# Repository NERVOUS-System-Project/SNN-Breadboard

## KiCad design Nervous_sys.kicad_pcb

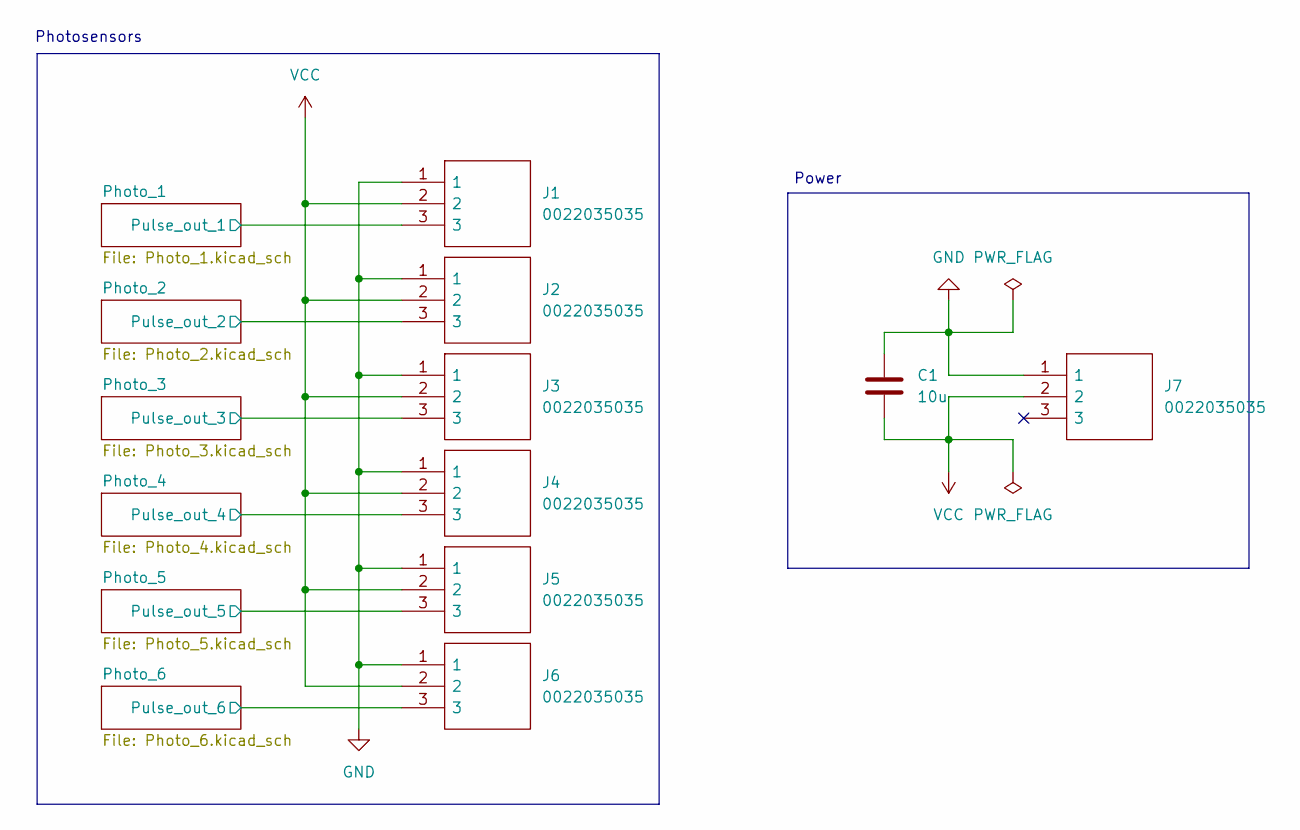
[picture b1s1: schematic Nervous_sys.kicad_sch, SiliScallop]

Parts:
C1: 10u; CP_Radial_D5.0mm_P2.00mm
J1, J2, J3, J4, J5, J6, J7: 0022035035; SHDR3W65P0X250_1X3_990X490X610P; Manufacturer_Part_Number 0022035035

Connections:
/Photo_1/Pulse_out_1: J1.3; also elsewhere on the board
/Photo_2/Pulse_out_2: J2.3; also elsewhere on the board
/Photo_3/Pulse_out_3: J3.3; also elsewhere on the board
/Photo_4/Pulse_out_4: J4.3; also elsewhere on the board
/Photo_5/Pulse_out_5: J5.3; also elsewhere on the board
/Photo_6/Pulse_out_6: J6.3; also elsewhere on the board
GND: C1.1, J1.1, J2.1, J3.1, J4.1, J5.1, J6.1, J7.1; also elsewhere on the board
VCC: C1.2, J1.2, J2.2, J3.2, J4.2, J5.2, J6.2, J7.2; also elsewhere on the board

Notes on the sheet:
Power
Photosensors

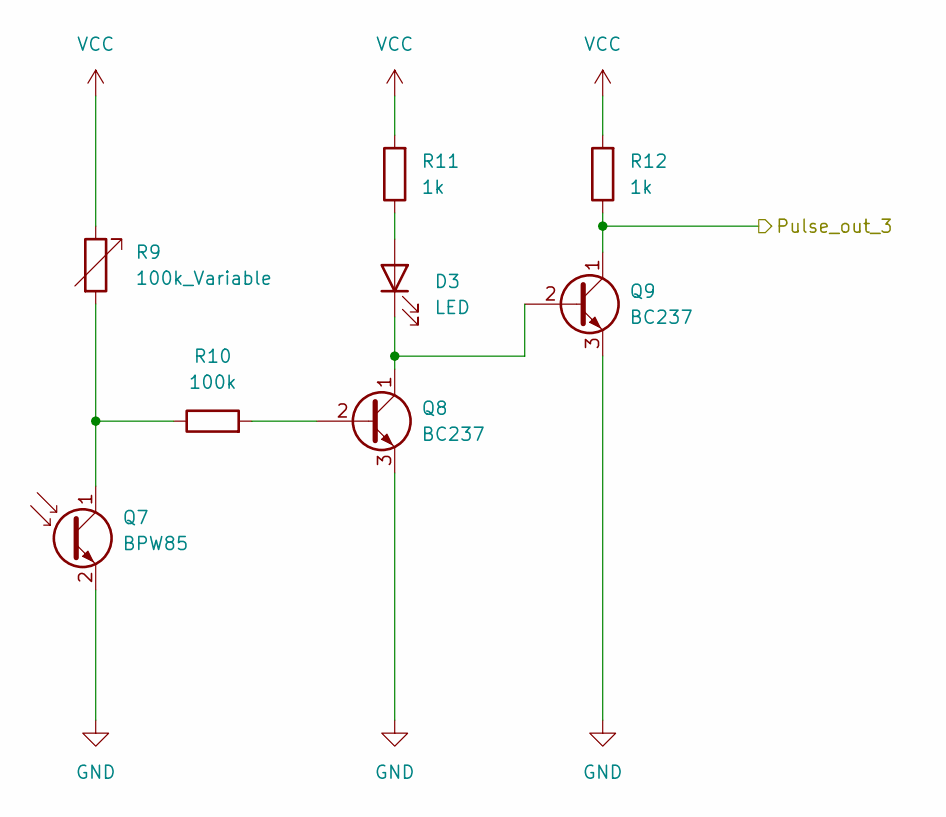
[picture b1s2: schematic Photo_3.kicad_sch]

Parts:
D3: LED; LED_D5.0mm
Q7: BPW85; LED_D3.0mm_Clear
Q8, Q9: BC237; TO-92_Inline
R9: 100k_Variable; Potentiometer_Bourns_3386P_Vertical
R10: 100k; R_Axial_DIN0207_L6.3mm_D2.5mm_P7.62mm_Horizontal
R11, R12: 1k; R_Axial_DIN0207_L6.3mm_D2.5mm_P7.62mm_Horizontal

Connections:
/Photo_3/Pulse_out_3: Q9.1 (C), R12.1; also elsewhere on the board
GND: Q7.2 (E), Q8.3 (E), Q9.3 (E); also elsewhere on the board
unnamed: D3.2 (A), R11.1
unnamed: D3.1 (K), Q8.1 (C), Q9.2 (B)
unnamed: Q7.1 (C), R9.2, R10.1
unnamed: Q8.2 (B), R10.2
VCC: R9.1, R11.2, R12.2; also elsewhere on the board

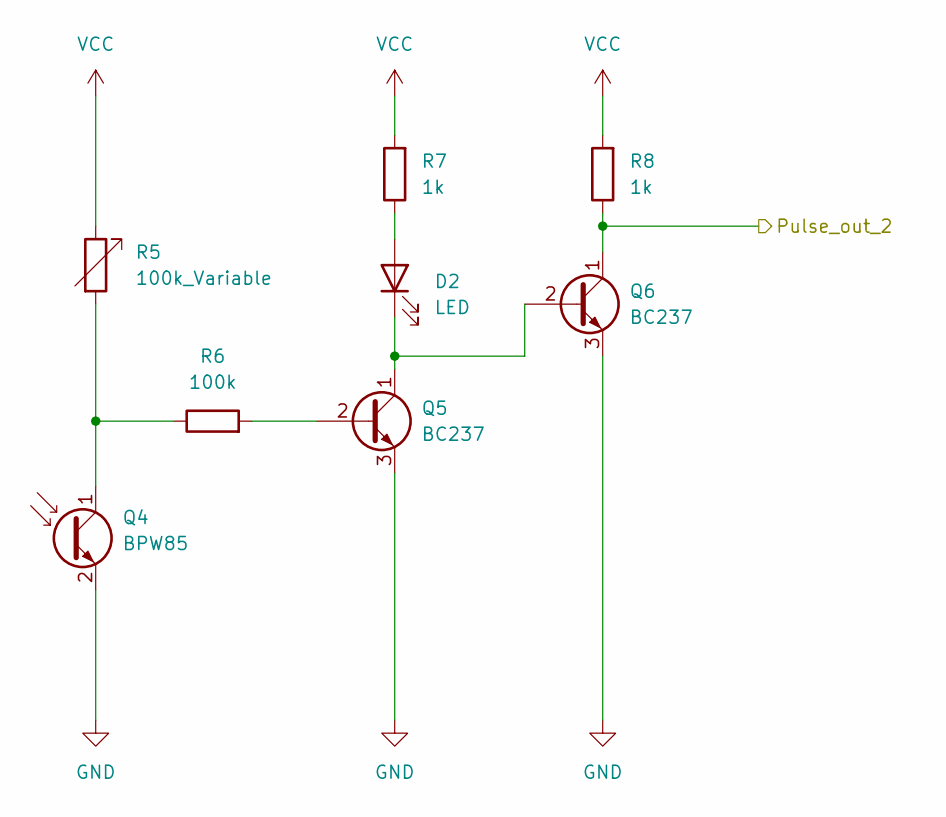
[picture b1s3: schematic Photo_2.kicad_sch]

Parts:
D2: LED; LED_D5.0mm
Q4: BPW85; LED_D3.0mm_Clear
Q5, Q6: BC237; TO-92_Inline
R5: 100k_Variable; Potentiometer_Bourns_3386P_Vertical
R6: 100k; R_Axial_DIN0207_L6.3mm_D2.5mm_P7.62mm_Horizontal
R7, R8: 1k; R_Axial_DIN0207_L6.3mm_D2.5mm_P7.62mm_Horizontal

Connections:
/Photo_2/Pulse_out_2: Q6.1 (C), R8.1; also elsewhere on the board
GND: Q4.2 (E), Q5.3 (E), Q6.3 (E); also elsewhere on the board
unnamed: D2.2 (A), R7.1
unnamed: D2.1 (K), Q5.1 (C), Q6.2 (B)
unnamed: Q4.1 (C), R5.2, R6.1
unnamed: Q5.2 (B), R6.2
VCC: R5.1, R7.2, R8.2; also elsewhere on the board

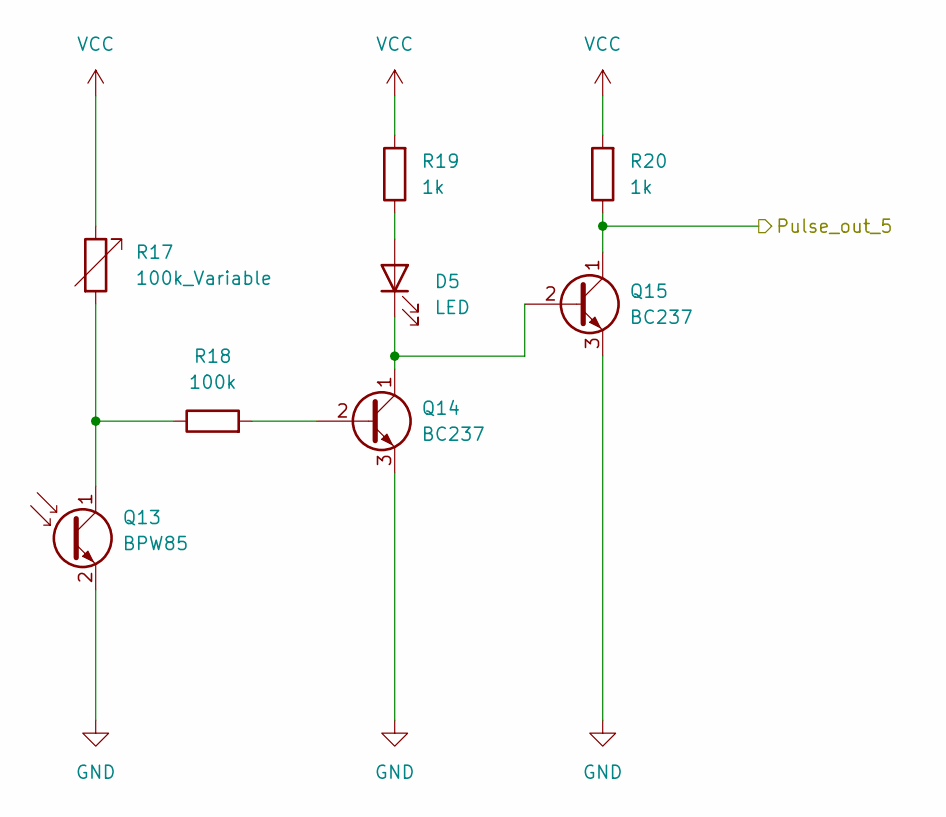
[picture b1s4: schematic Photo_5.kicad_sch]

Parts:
D5: LED; LED_D5.0mm
Q13: BPW85; LED_D3.0mm_Clear
Q14, Q15: BC237; TO-92_Inline
R17: 100k_Variable; Potentiometer_Bourns_3386P_Vertical
R18: 100k; R_Axial_DIN0207_L6.3mm_D2.5mm_P7.62mm_Horizontal
R19, R20: 1k; R_Axial_DIN0207_L6.3mm_D2.5mm_P7.62mm_Horizontal

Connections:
/Photo_5/Pulse_out_5: Q15.1 (C), R20.1; also elsewhere on the board
GND: Q13.2 (E), Q14.3 (E), Q15.3 (E); also elsewhere on the board
unnamed: D5.2 (A), R19.1
unnamed: D5.1 (K), Q14.1 (C), Q15.2 (B)
unnamed: Q13.1 (C), R17.2, R18.1
unnamed: Q14.2 (B), R18.2
VCC: R17.1, R19.2, R20.2; also elsewhere on the board

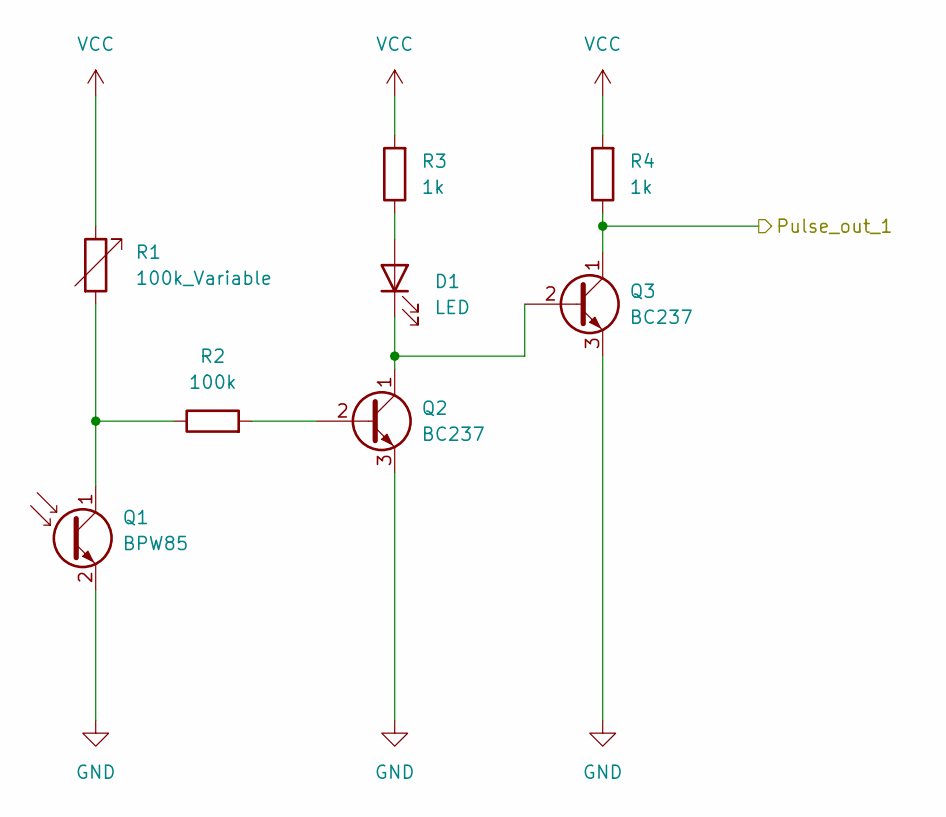
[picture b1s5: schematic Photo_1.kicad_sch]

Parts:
D1: LED; LED_D5.0mm
Q1: BPW85; LED_D3.0mm_Clear
Q2, Q3: BC237; TO-92_Inline
R1: 100k_Variable; Potentiometer_Bourns_3386P_Vertical
R2: 100k; R_Axial_DIN0207_L6.3mm_D2.5mm_P7.62mm_Horizontal
R3, R4: 1k; R_Axial_DIN0207_L6.3mm_D2.5mm_P7.62mm_Horizontal

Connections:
/Photo_1/Pulse_out_1: Q3.1 (C), R4.1; also elsewhere on the board
GND: Q1.2 (E), Q2.3 (E), Q3.3 (E); also elsewhere on the board
unnamed: D1.2 (A), R3.1
unnamed: D1.1 (K), Q2.1 (C), Q3.2 (B)
unnamed: Q1.1 (C), R1.2, R2.1
unnamed: Q2.2 (B), R2.2
VCC: R1.1, R3.2, R4.2; also elsewhere on the board

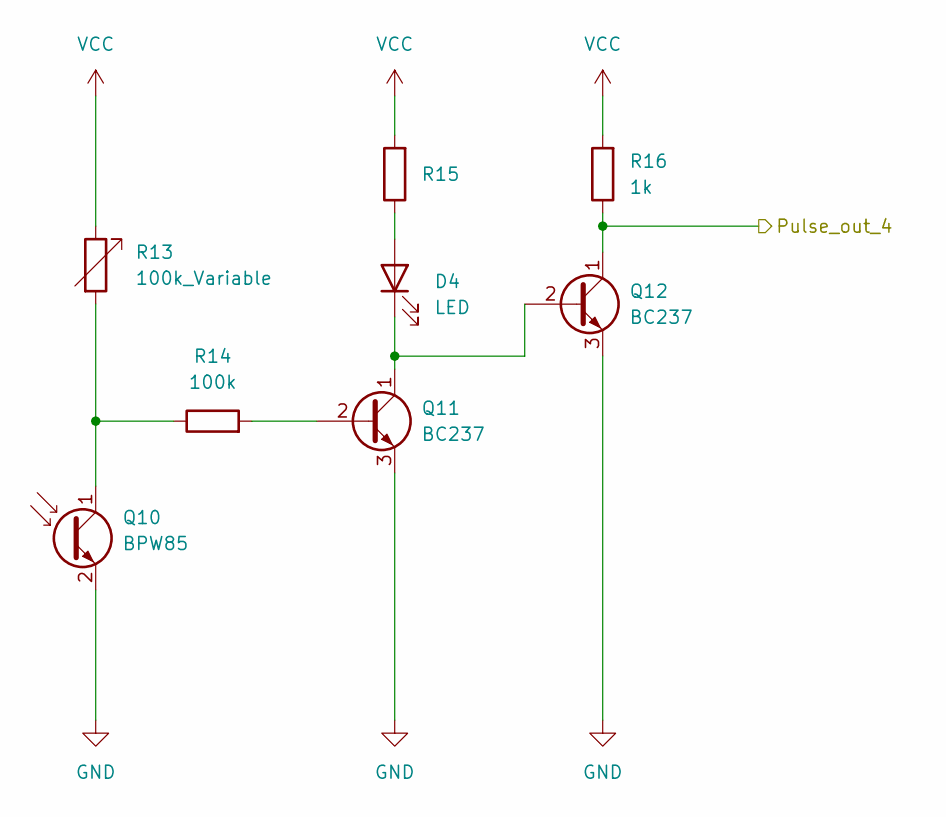
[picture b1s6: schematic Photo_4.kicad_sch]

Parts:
D4: LED; LED_D5.0mm
Q10: BPW85; LED_D3.0mm_Clear
Q11, Q12: BC237; TO-92_Inline
R13: 100k_Variable; Potentiometer_Bourns_3386P_Vertical
R14: 100k; R_Axial_DIN0207_L6.3mm_D2.5mm_P7.62mm_Horizontal
R15, R16: 1k; R_Axial_DIN0207_L6.3mm_D2.5mm_P7.62mm_Horizontal

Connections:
/Photo_4/Pulse_out_4: Q12.1 (C), R16.1; also elsewhere on the board
GND: Q10.2 (E), Q11.3 (E), Q12.3 (E); also elsewhere on the board
unnamed: D4.2 (A), R15.1
unnamed: D4.1 (K), Q11.1 (C), Q12.2 (B)
unnamed: Q10.1 (C), R13.2, R14.1
unnamed: Q11.2 (B), R14.2
VCC: R13.1, R15.2, R16.2; also elsewhere on the board

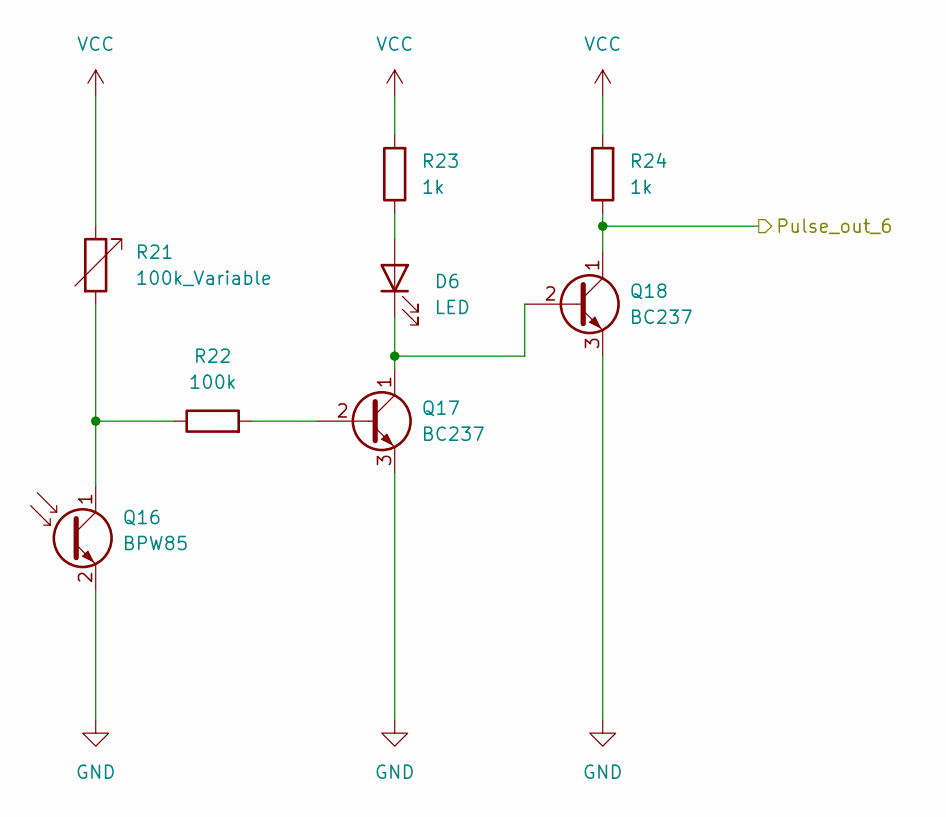
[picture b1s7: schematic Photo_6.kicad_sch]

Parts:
D6: LED; LED_D5.0mm
Q16: BPW85; LED_D3.0mm_Clear
Q17, Q18: BC237; TO-92_Inline
R21: 100k_Variable; Potentiometer_Bourns_3386P_Vertical
R22: 100k; R_Axial_DIN0207_L6.3mm_D2.5mm_P7.62mm_Horizontal
R23, R24: 1k; R_Axial_DIN0207_L6.3mm_D2.5mm_P7.62mm_Horizontal

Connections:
/Photo_6/Pulse_out_6: Q18.1 (C), R24.1; also elsewhere on the board
GND: Q16.2 (E), Q17.3 (E), Q18.3 (E); also elsewhere on the board
unnamed: D6.2 (A), R23.1
unnamed: D6.1 (K), Q17.1 (C), Q18.2 (B)
unnamed: Q16.1 (C), R21.2, R22.1
unnamed: Q17.2 (B), R22.2
VCC: R21.1, R23.2, R24.2; also elsewhere on the board

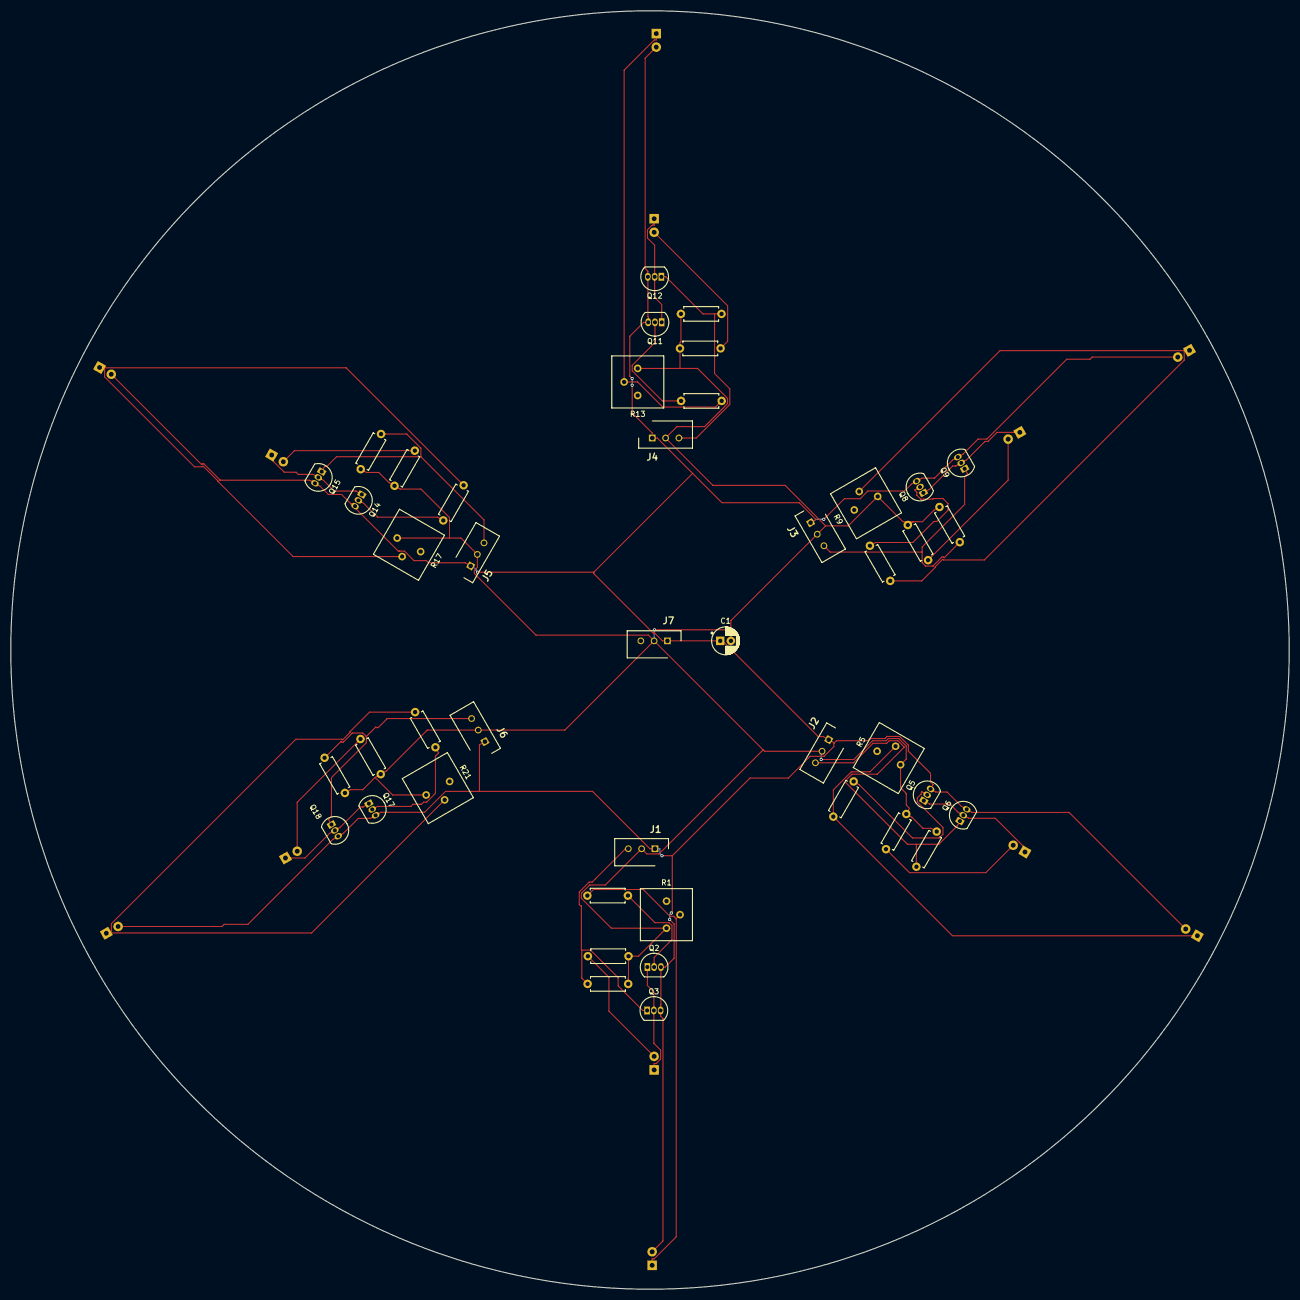
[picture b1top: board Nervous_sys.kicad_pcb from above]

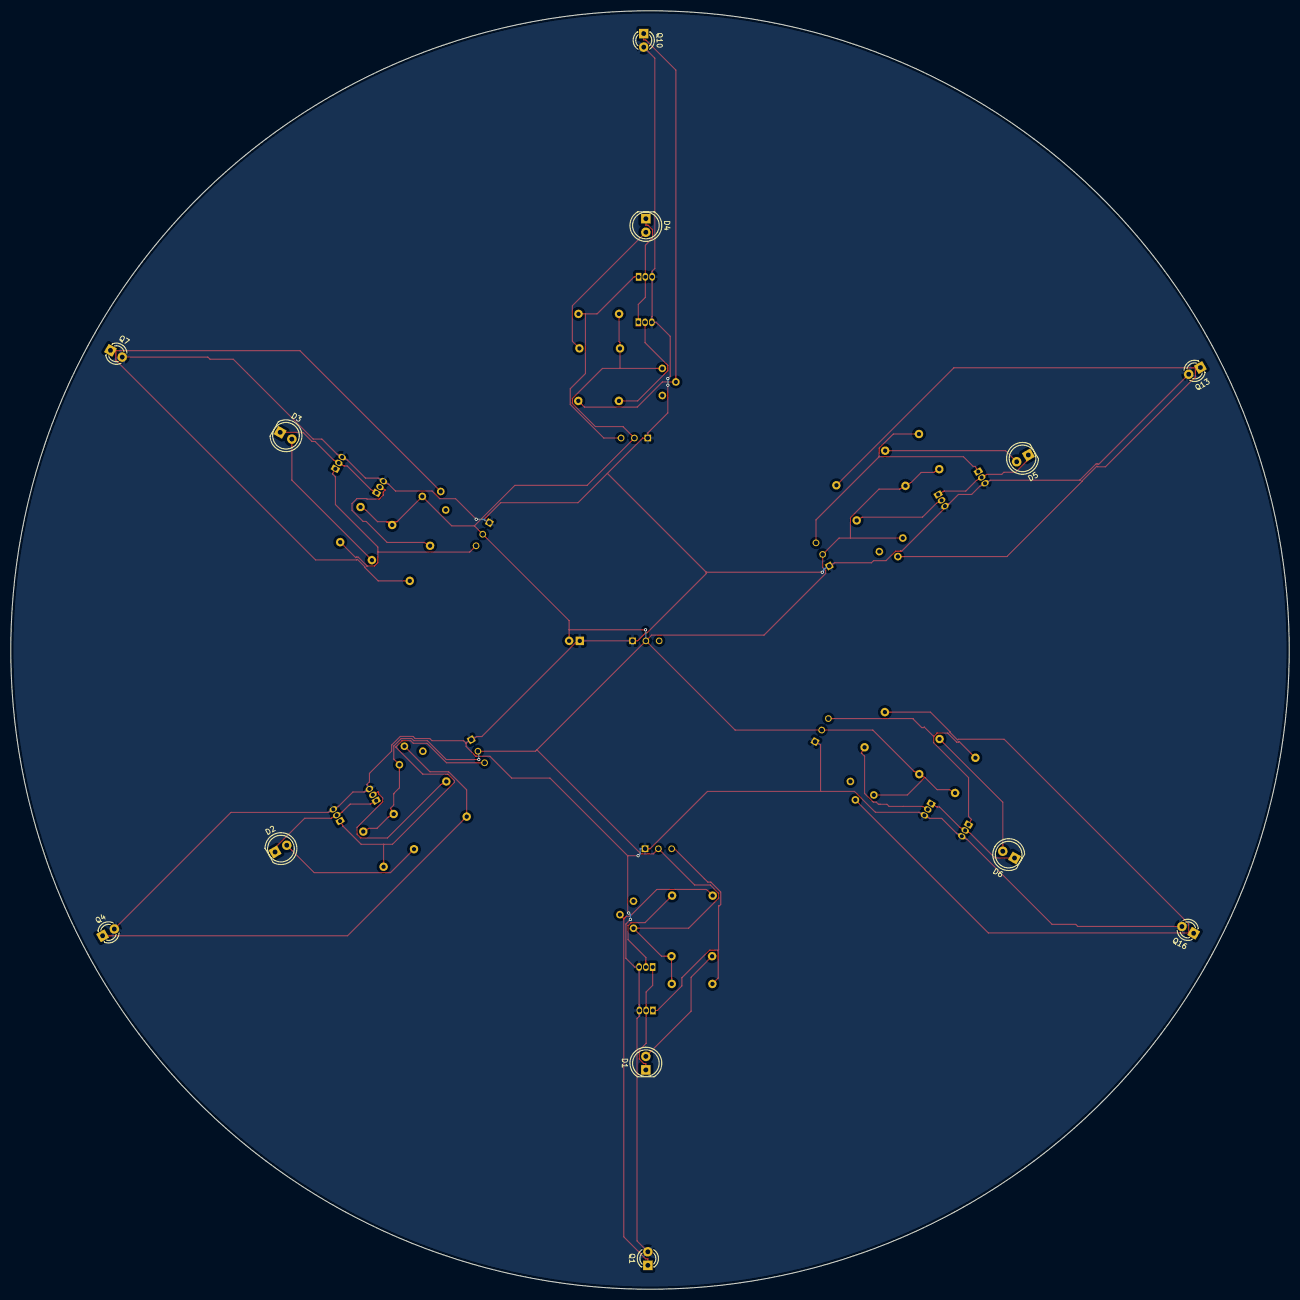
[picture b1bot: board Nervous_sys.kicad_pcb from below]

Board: 2 copper layers, 240.0 x 240.0 mm, 56 parts (12 on the bottom side), 32 nets.

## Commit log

2024-08-12 add controller PCB
